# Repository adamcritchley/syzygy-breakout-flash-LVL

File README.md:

# SYZYGY Breakout Flash with Level Shifters
SYZYGY Breakout Board with level shifters for any voltage flash chip. I wanted a way to experiment with flash without having to spin a new board for each footprint or solder yet another BGA or TSOP. Flash programmers with ZIF adapters seemed like the best choice and SYZYGY would make it compatible with a wide range of FPGA boards. So I combined the ZIF and SYZYGY then added a clock and level shifters. This is the mid range version of the other two SYZYGY flash breakout boards and requires 1.8V VIO to shift logic properly so do not change the request VIO in the SYZYGY DNA. It even works with ZUBoard 1CG's dumb VIO.

# Building Firmware
A prebuilt firmware has been provided in the 'firmware' directory. I don't recommend changing VIO for this board since it has built-in level shifters. However, if you want to really want to customize the SMART VIO then modify 'szg-flash-std.json' with the custom voltage and power and use the official [SYZYGY tools](https://github.com/SYZYGYfpga/syzygy-tools/) repo to build the firmware. Note that the voltage reference for the level shifters is connected directly to the 1.8V LDO.
```bash
python ..\..\syzygy-tools\dna-tools\syzygy-tools.py -d ..\szg-dna\SZG-FLASH\szg-flash-std.json -f ..\..\syzygy-tools\pod-fw\avr-dna-fw-main.hex
```

# Fabrication
I use JLCPCB and OSH Park. I used the DRC rules for OSH Park so the board doesn't have any special fabrication requirements. Just pick your favorite PCB shop and color.

# FPGA Development
The board has silkscreen text with corresponding pins for Avnet's [ZUBoard 1CG](https://www.avnet.com/wps/portal/us/products/avnet-boards/avnet-board-families/zuboard-1cg/). If you use a different board then you'll have to change the silkscreen and generate new gerbers. Or you can just look up the pins for your board each time. Theoretically you can use this board with any FPGA dev board that has a SYZYGY connector then you could use the respective controller for your flash device OR find someway to expose it to AXI and PS to use it with flashrom. As I figure out specific tools that work well then I'll update this README with tutorials.

# BOM
You can find datasheets for each component in the datasheets directory. All of the components can be bought from Mouser or Digikey. 
* Epson SG5032VAN
* Texas Instrument TLV1117LV
* Texas Instrument TXS0108EQPWRQ1
* Aries 28-6554-11

# Future Work
I consider this board feature complete. As I find/create IP and software that works with this board then I'll update this README with tutorials on how to use them. Feel free to create a GitHub issue detailing your own success story or use case.

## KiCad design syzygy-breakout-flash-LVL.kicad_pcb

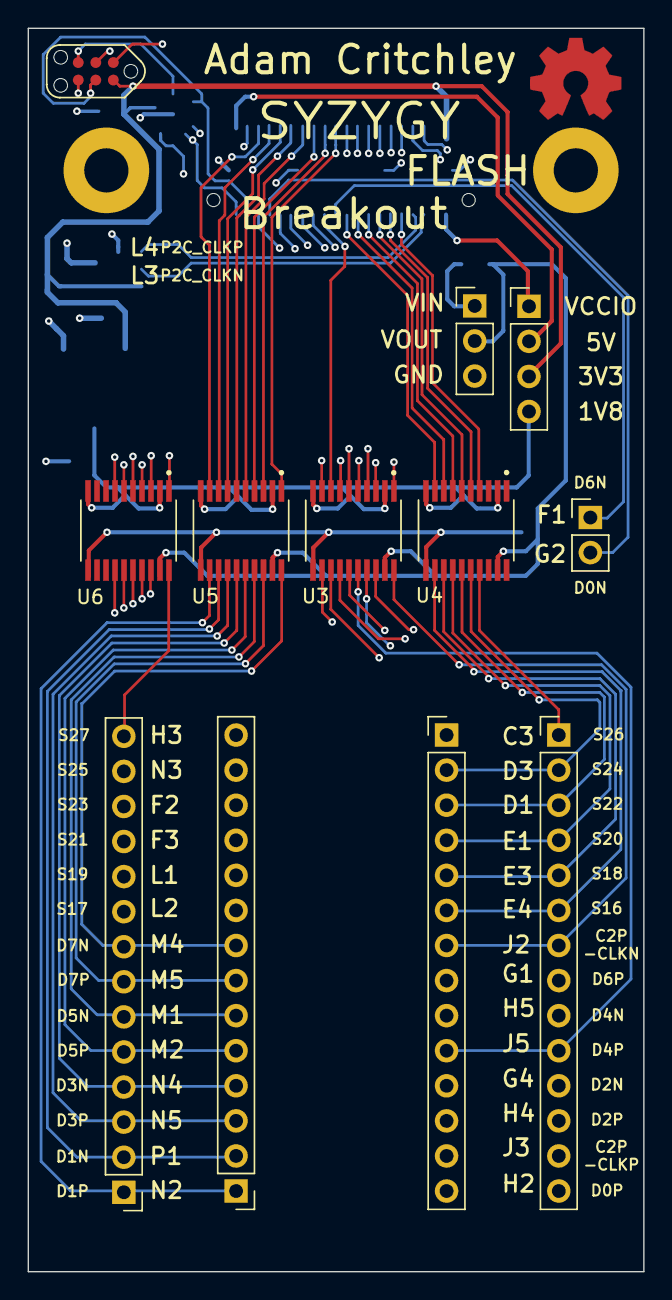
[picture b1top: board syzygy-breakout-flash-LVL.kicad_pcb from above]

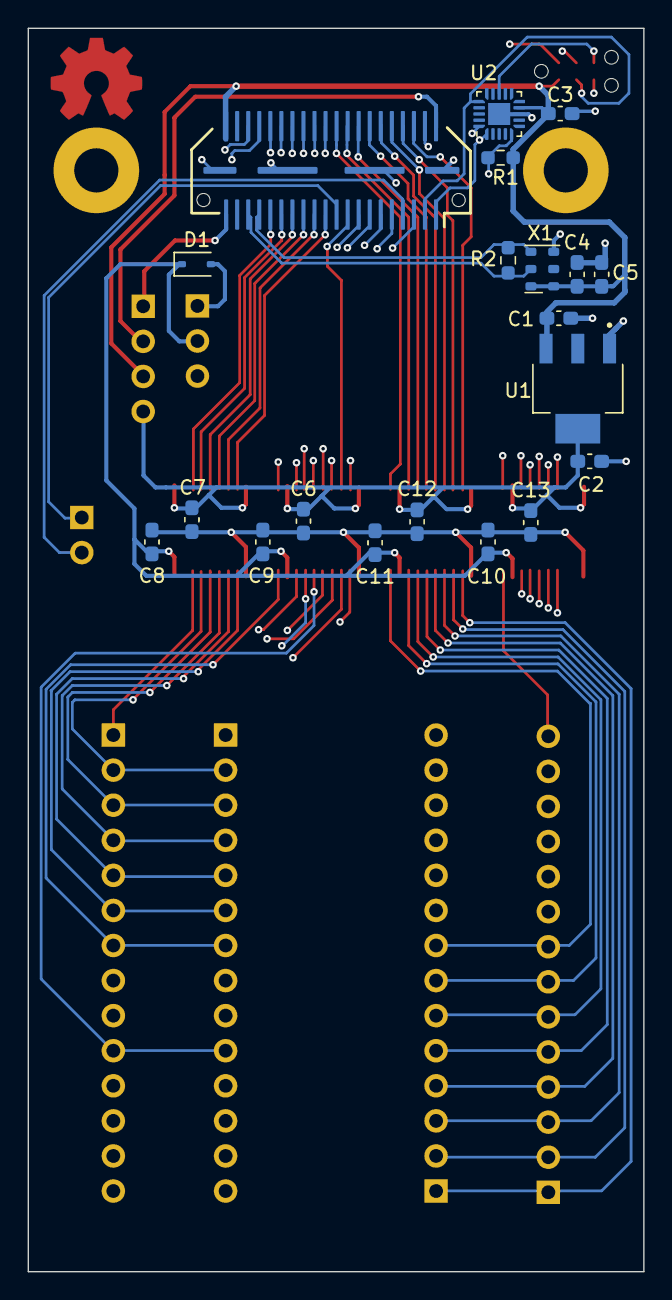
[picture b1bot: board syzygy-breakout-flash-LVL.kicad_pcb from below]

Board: 4 copper layers, 44.6 x 90.0 mm, 32 parts (20 on the bottom side), 72 nets.

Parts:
C1, C2, C4: 1uF; C_0603_1608Metric_Pad1.08x0.95mm_HandSolder
C3, C5, C6, C7, C8, C9, C10, C11, C12, C13: 0.1uF; C_0603_1608Metric_Pad1.08x0.95mm_HandSolder
D1: BAT60A; D_SOD-323
J1: SYZYGY-STD; SYZYGY-STD-POD
J2, J3, J8, J9: Conn_01x14; PinHeader_1x14_P2.54mm_Vertical
J4: Conn_01x04; PinHeader_1x04_P2.54mm_Vertical
J5: Conn_01x03; PinHeader_1x03_P2.54mm_Vertical
J6: TagConnect; TC2030-NL_SMALL
J10: Conn_01x02; PinHeader_1x02_P2.54mm_Vertical
R1: 10K; R_0603_1608Metric_Pad0.98x0.95mm_HandSolder
R2: 100R; R_0603_1608Metric_Pad0.98x0.95mm_HandSolder
U1: TLV1117LV18DCYT; SOT230P700X180-4N
U2: ATtiny44A-MMH; QFN-20-1EP_3x3mm_P0.45mm_EP1.6x1.6mm
U3, U4, U5, U6: TXS0108EQPWRQ1; SOP65P640X120-20N
X1: SG3225VAN; Oscillator_SMD_Silicon_Labs_LGA-6_2.5x3.2mm_P1.25mm

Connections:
+1V8: C2.1, C6.1, C7.1, C12.1, C13.1, J4.4, U1.4 (VOUT), U3.2 (VCCA), U3.10 (OE), U4.2 (VCCA), U4.10 (OE), U5.2 (VCCA), U5.10 (OE), U6.2 (VCCA), U6.10 (OE)
+3V3: C1.2, C3.1, C4.1, C5.1, J1.40 (+3.3V), J4.3, J6.2, R1.1, U1.3 (IN), U2.9 (VCC), X1.1 (OE), X1.6 (Vcc)
+5V: J1.2 (+5V), J4.2
/C2P_CLKN: J1.36 (C2P_CLKN), U3.1 (A1)
/C2P_CLKP: J1.34 (C2P_CLKP), U3.3 (A2)
/D0_N: J1.7 (S2_D0N), J10.2
/D0_P: J1.5 (S0_D0P), U3.9 (A8)
/D1_N: J1.8 (S3_D1N), U5.8 (A7)
/D1_P: J1.6 (S1_D1P), U5.9 (A8)
/D2_N: J1.11 (S6_D2N), U3.6 (A5)
/D2_P: J1.9 (S4_D2P), U3.7 (A6)
/D3_N: J1.12 (S7_D3N), U5.6 (A5)
/D3_P: J1.10 (S5_D3P), U5.7 (A6)
/D4_N: J1.15 (S10_D4N), U3.4 (A3)
/D4_P: J1.13 (S8_D4P), U3.5 (A4)
/D5_N: J1.16 (S11_D5N), U5.4 (A3)
/D5_P: J1.14 (S9_D5P), U5.5 (A4)
/D6_N: J1.19 (S14_D6N), J10.1
/D6_P: J1.17 (S12_D6P), U3.8 (A7)
/D7_N: J1.20 (S15_D7N), U5.1 (A1)
/D7_P: J1.18 (S13_D7P), U5.3 (A2)
/P2C_CLK_N: J1.35 (P2C_CLKN), R2.1, X1.5 (~OUT)
/P2C_CLK_P: J1.33 (P2C_CLKP), R2.2, X1.4 (OUT)
/Peripheral MCU/MISO: J6.1, U2.20 (PA5)
/Peripheral MCU/~RESET: J6.5, U2.13 (~RESET/PB3)
/RGA: J1.4 (R_GA), R1.2, U2.5 (AREF/PA0)
/S16: J1.21 (S16), U4.9 (A8)
/S17: J1.22 (S17), U6.7 (A6)
/S18: J1.23 (S18), U4.8 (A7)
/S19: J1.24 (S19), U6.6 (A5)
/S20: J1.25 (S20), U4.7 (A6)
/S21: J1.26 (S21), U6.5 (A4)
/S22: J1.27 (S22), U4.6 (A5)
/S23: J1.28 (S23), U6.4 (A3)
/S24: J1.29 (S24), U4.5 (A4)
/S25: J1.30 (S25), U6.3 (A2)
/S26: J1.31 (S26), U4.4 (A3)
/S27: J1.32 (S27), U6.1 (A1)
/SCL: J1.1 (SCL), J6.3, U2.1 (PA4)
/SDA: J1.3 (SDA), J6.4, U2.16 (PA6)
GND: C1.1, C2.2, C3.2, C4.2, C5.2, C6.2, C7.2, C8.2, C9.2, C10.2, C11.2, C12.2, C13.2, J1.41 (GND), J5.3, J6.6, U1.1 (GND), U2.8 (GND), U2.21 (GND), U3.11 (GND), U4.11 (GND), U5.11 (GND), U6.11 (GND), X1.3 (GND)
unnamed: D1.2 (A), J5.1
unnamed: J2.1, J9.1, U4.17 (B3)
unnamed: J2.2, J9.2, U4.16 (B4)
unnamed: J2.3, J9.3, U4.15 (B5)
unnamed: J2.4, J9.4, U4.14 (B6)
unnamed: J2.5, J9.5, U4.13 (B7)
unnamed: J2.6, J9.6, U4.12 (B8)
unnamed: J2.7, J9.7, U3.20 (B1)
unnamed: J2.8, J9.8, U3.13 (B7)
unnamed: J2.9, J9.9, U3.17 (B3)
unnamed: J2.10, J9.10, U3.16 (B4)
unnamed: J2.11, J9.11, U3.15 (B5)
unnamed: J2.12, J9.12, U3.14 (B6)
unnamed: J2.13, J9.13, U3.18 (B2)
unnamed: J2.14, J9.14, U3.12 (B8)
unnamed: J3.1, J8.1, U5.12 (B8)
unnamed: J3.2, J8.2, U5.13 (B7)
unnamed: J3.3, J8.3, U5.14 (B6)
unnamed: J3.4, J8.4, U5.15 (B5)
unnamed: J3.5, J8.5, U5.16 (B4)
unnamed: J3.6, J8.6, U5.17 (B3)
unnamed: J3.7, J8.7, U5.18 (B2)
unnamed: J3.8, J8.8, U5.20 (B1)
unnamed: J3.9, J8.9, U6.14 (B6)
unnamed: J3.10, J8.10, U6.15 (B5)
unnamed: J3.11, J8.11, U6.16 (B4)
unnamed: J3.12, J8.12, U6.17 (B3)
unnamed: J3.13, J8.13, U6.18 (B2)
unnamed: J3.14, J8.14, U6.20 (B1)
VCC: C8.1, C9.1, C10.1, C11.1, D1.1 (K), J5.2, U3.19 (VCCB), U4.19 (VCCB), U5.19 (VCCB), U6.19 (VCCB)
VCCIO: J1.39 (VIO1), J4.1

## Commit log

2023-09-09 Create LICENSE
2023-09-09 Add SYZYGY DNA
2023-09-18 Add board images to repo
2023-10-14 Added default SZG DNA firmware. Updated README.md
